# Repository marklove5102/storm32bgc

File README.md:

STorM32 BGC
===========

<strong>STM32 32-bit microcontroller based 3-axis brushless gimbal controller board</strong>

schemes and designs by OlliW (except of STorM32 v4.1)<br>
v0.17: layout by Martinez and OlliW<br>
v4.1: design by KrattWorks

latest board version: v3.3, v4.1, v6.2

The STorM32 BGC boards and all other hardware published here are open source hardware, under the terms of the TAPR Open Hardware License as published by the Free Hardware Foundation, see http://www.tapr.org/ohl.html.

The firmwares are free and the GUI is open source, for the details of the terms of usage/licenses see <a href="http://www.olliw.eu/2013/storm32bgc">here</a>.

<strong>Further resources:</strong><br>- project web page http://www.olliw.eu/2013/storm32bgc (out-dated)/<br>- thread at rcgroups http://www.rcgroups.com/forums/showthread.php?t=2055844<br>- wiki for the documentation http://www.olliw.eu/storm32bgc-wiki/

## STorM32 v6.2 Board

General purpose boards specifically made for NT and TSTorM32 setups. STM32H7 based.

## STorM32 v4.1 Board

General purpose board, like v3.3 but with on-board motor drivers.

## STorM32 v3.3 Boards

General purpose boards specifically made for NT and TSTorM32 setups.

### STorM32 Micro Series

Series of stackable boards with 20x20 mm hole pattern: Main board, NT Motor-Encoder module, NT Triple Motor module, NT Logger module. 

<strong>changes in v3.3:</strong><br>- board specifically designed for NT and T-STorM32<br>- no motor drivers on board<br>- 3 NT plugs to make it easy to connect several NT modules<br>- NT-X plug carrying also the battery voltage<br>- 5 V power rail on the NT bus, with sufficient "juice"<br>- Rx&Tx on NT bus swapped, to avoid cable crossing to connect with NT modules<br>- support of stacking with a "high-power" extension board<br>- MPU9250 on board, spi (no i2c anymore!)<br>- firmware update procedure via USB<br>- ESP8266 port for WIFI connectability<br>- CAN bus port<br>- no BOOT0 button, smaller RESET button<br>- 0402 size parts<br>- board size as small as I could get it with a 2 layer design: 40 x 25 mm<br>- mounting holes, 3 mm diameter, 35 mm apart

## v1.x Boards

These boards will be phased out.

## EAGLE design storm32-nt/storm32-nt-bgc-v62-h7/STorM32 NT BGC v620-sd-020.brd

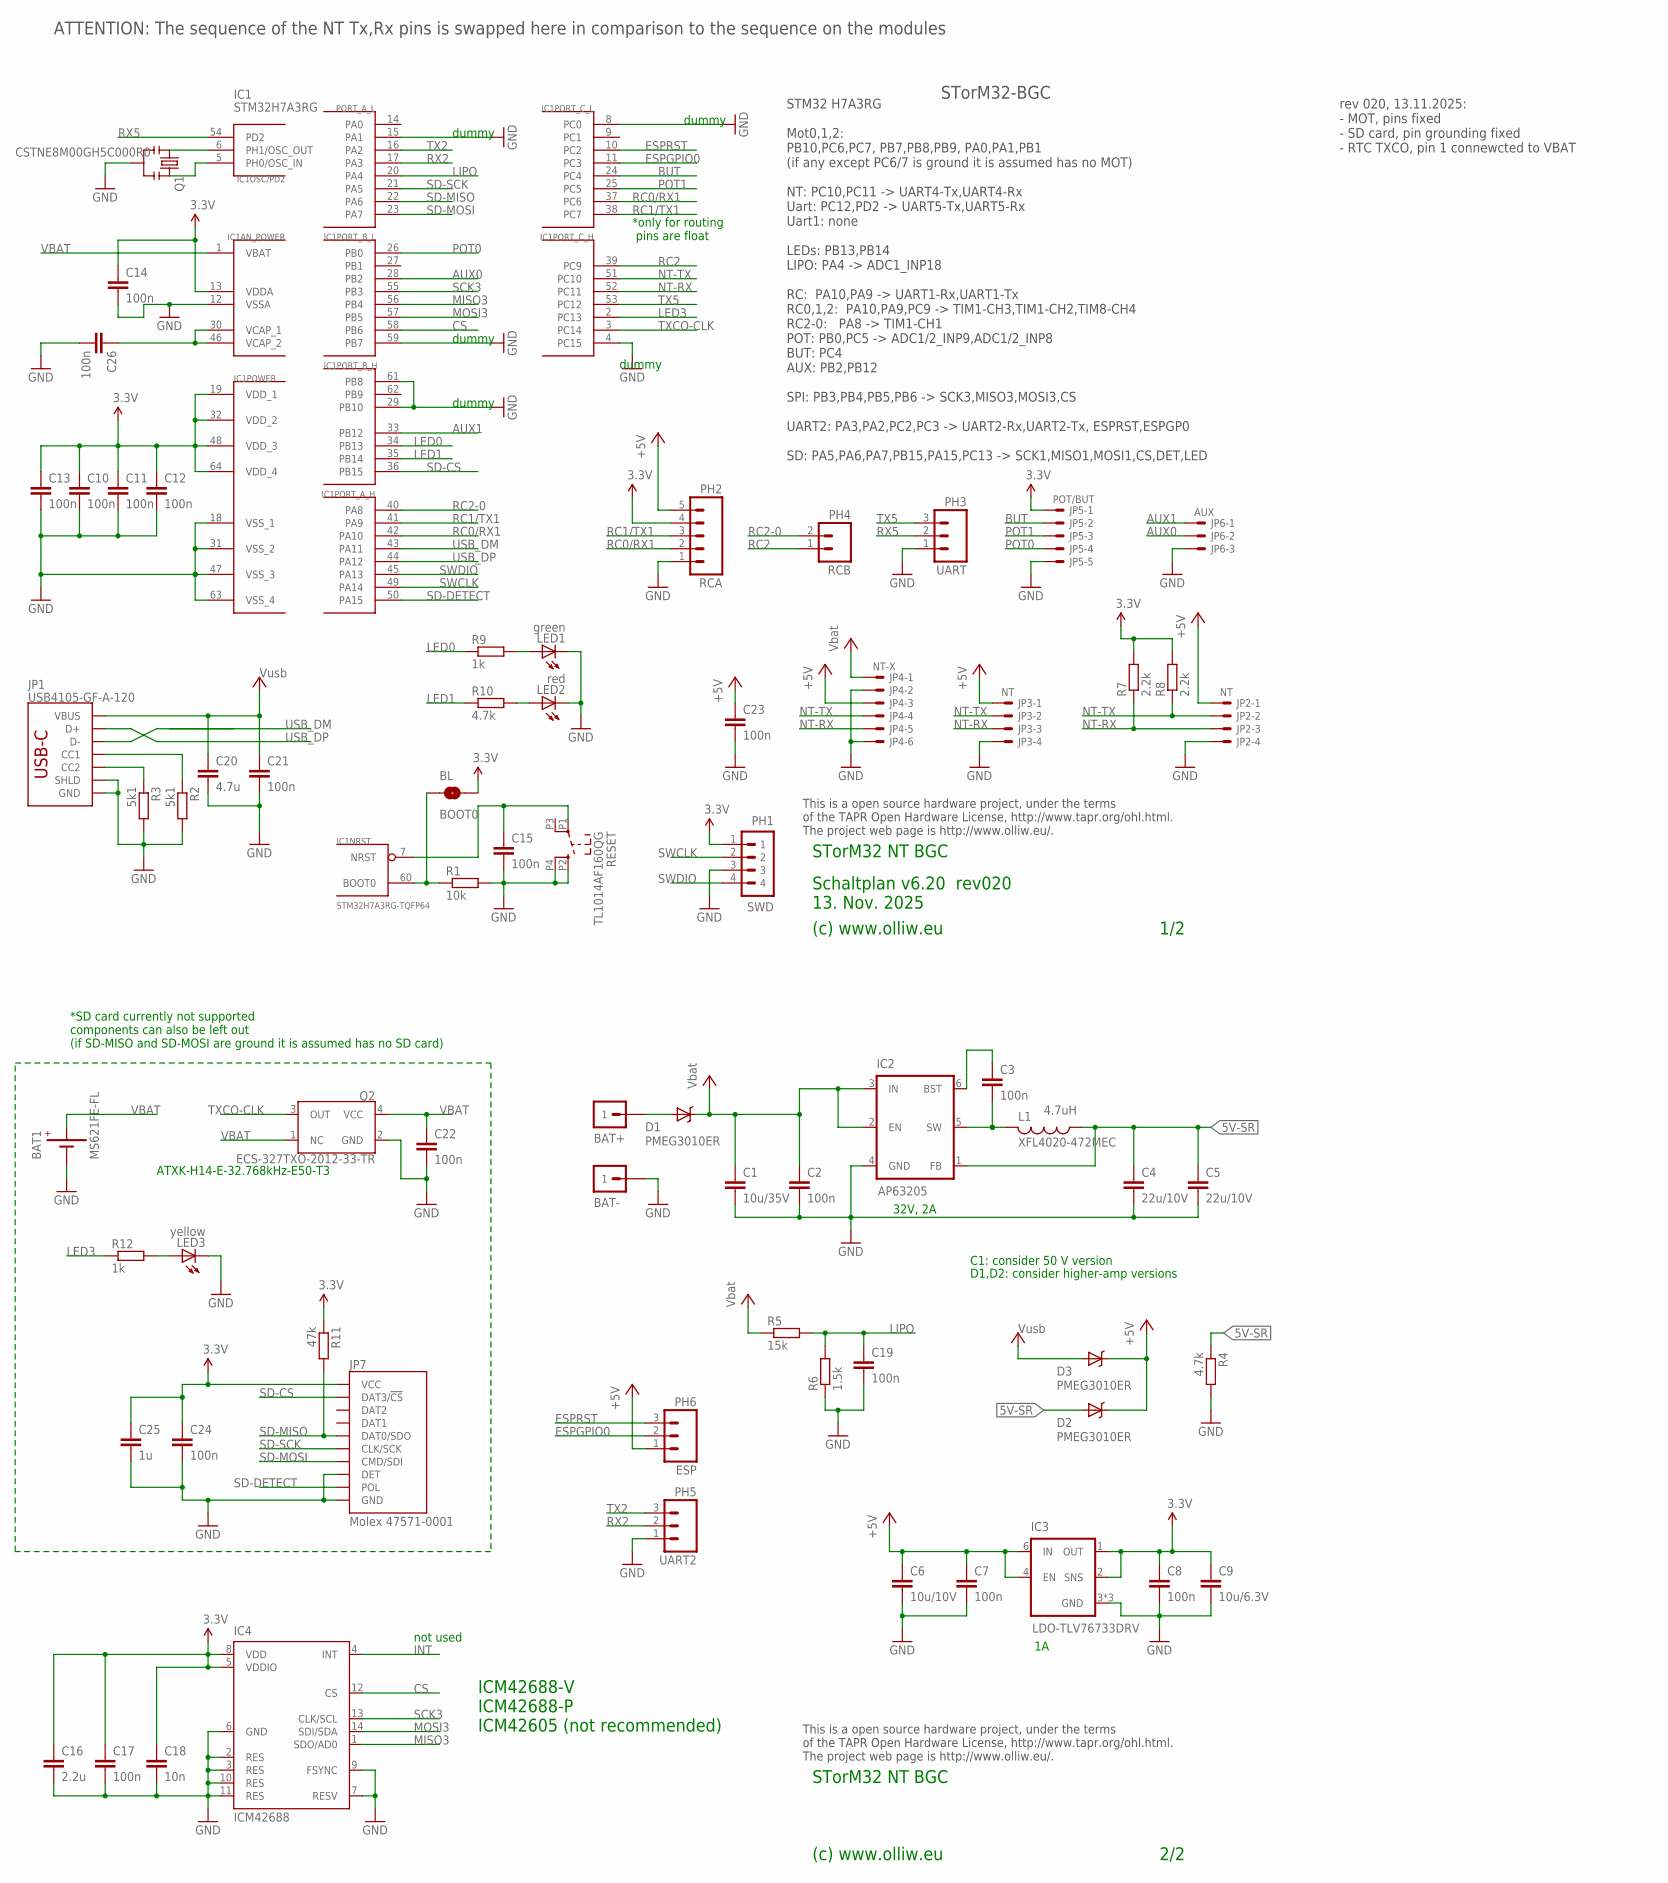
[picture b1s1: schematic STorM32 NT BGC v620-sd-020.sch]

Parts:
BAT1: MS621FE-FL; CELL-RECHARGABLE-6P8
BAT+: M1X1; 1X1_WITHOUT
BAT-: M1X1; 1X1_WITHOUT
BL: BOOT0; SJ_2S-NO
C1: 10u/35V; C1206K
C2: 100n; C0603
C3, C7, C8, C10, C11, C12, C13, C14, C15, C17, C19, C21, C22, C23, C24, C26: 100n; C0402
C4, C5: 22u/10V; C0805K
C6: 10u/10V; C0805K
C9: 10u/6.3V; C0805K
C16: 2.2u; C0603
C18: 10n; C0402
C20: 4.7u; C0603
C25: 1u; C0402
D1, D2, D3: PMEG3010ER; SOD123W-DIODE
IC1: STM32H7A3RG-TQFP64; TQFP64
IC2: AP63205; SOT23-6
IC3: LDO-TLV76733DRV; WSON-6-2X2
IC4: ICM42688; LGA14-2.5X3
JP1: USB4105-GF-A-120; USB-C
JP2, JP3: NT; SM04B-SRSS-TB
JP4: NT-X; SM06B-SRSS-TB
JP5: POT/BUT; SM05B-SRSS-TB
JP6: AUX; SM03B-SRSS-TB
JP7: Molex 47571-0001; SD-MICRO-SHORT
L1: XFL4020-472MEC; L4X4
LED1: green; CHIPLED_0603
LED2: red; CHIPLED_0603
LED3: yellow; CHIPLED_0603
PH1: SWD; 4X1_1P27_OCT_BILEX
PH2: RCA; 1X05
PH3: UART; 1X03_NO_SILK
PH4: RCB; 1X02_NO_SILK
PH5: UART2; 1X03_NO_SILK
PH6: ESP; 1X03_NO_SILK
Q1: CSTNE8M00GH5C000R0; RESONATOR-SMD
Q2: ECS-327TXO-2012-33-TR; TXCO-20X12
R1: 10k; R0402
R2, R3: 5k1; R0402
R4, R10: 4.7k; R0402
R5: 15k; R0402
R6: 1.5k; R0402
R7, R8: 2.2k; R0402
R9, R12: 1k; R0402
R11: 47k; R0402
RESET: TL1014AF160QG; TACTILE-SWITCH-SMD-RIGHT-TL1014

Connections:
3.3V: BL.2, C8.1, C9.1, C10.1, C11.1, C12.1, C13.1, C14.1, C16.1, C17.1, C18.1, C24.1, C25.1, IC1.13 (VDDA), IC1.19 (VDD_1), IC1.32 (VDD_2), IC1.48 (VDD_3), IC1.64 (VDD_4), IC3.1 (OUT), IC3.2 (SNS), IC4.5 (VDDIO), IC4.8 (VDD), JP5.1, JP7.4 (VCC), PH1.1, PH2.4, R7.2, R8.2, R11.1
5V-SR: C4.1, C5.1, D2.A, IC2.1 (FB), L1.1, R4.1
+5V: C6.1, C7.1, C23.1, D2.C, D3.C, IC3.4 (EN), IC3.6 (IN), JP2.1, JP3.1, JP4.3, PH2.5, PH6.1
AUX0: IC1.28 (PB2), JP6.2
AUX1: IC1.33 (PB12), JP6.1
BATP: BAT+.1, D1.A
BOOT0: BL.1, IC1.60 (BOOT0), R1.1
BUT: IC1.24 (PC4), JP5.2
CS: IC1.58 (PB6), IC4.12 (CS)
ESPGPIO0: IC1.11 (PC3), PH6.2
ESPRST: IC1.10 (PC2), PH6.3
GND: BAT1.P- (GND), BAT-.1, C1.2, C2.2, C4.2, C5.2, C6.2, C7.2, C8.2, C9.2, C10.2, C11.2, C12.2, C13.2, C14.2, C15.2, C16.2, C17.2, C18.2, C19.2, C20.2, C21.2, C22.2, C23.2, C24.2, C25.2, C26.2, IC1.4 (PC15), IC1.8 (PC0), IC1.12 (VSSA), IC1.15 (PA1), IC1.18 (VSS_1), IC1.29 (PB10), IC1.31 (VSS_2), IC1.47 (VSS_3), IC1.59 (PB7), IC1.61 (PB8), IC1.63 (VSS_4), IC2.4 (GND), IC3.3 (GND), IC3.5 (GND), IC3.7 (GND), IC4.2 (RES), IC4.3 (RES), IC4.6 (GND), IC4.7 (RESV), IC4.9 (FSYNC), IC4.10 (RES), IC4.11 (RES), JP1.GND, JP1.GND2 (GND), JP1.SHLD1 (SHLD), JP1.SHLD2 (SHLD), JP1.SHLD3 (SHLD), JP1.SHLD4 (SHLD), JP2.4, JP3.4, JP4.2, JP4.6, JP5.5, JP6.3, JP7.6 (GND), JP7.G4 (DET), JP7.GND1 (GND), JP7.GND2 (GND), LED1.C, LED2.C, LED3.C, PH1.3, PH2.1, PH3.1, PH5.1, Q1.2, Q2.2 (GND), R1.2, R2.2, R3.2, R4.2, R6.1, RESET.P2 (1), RESET.P4 (2)
INT: IC4.4 (INT)
LED0: IC1.34 (PB13), R9.1
LED1: IC1.35 (PB14), R10.1
LED3: IC1.2 (PC13), R12.1
LIPO: C19.1, IC1.20 (PA4), R5.2, R6.2
MISO3: IC1.56 (PB4), IC4.1 (SDO/AD0)
MOSI3: IC1.57 (PB5), IC4.14 (SDI/SDA)
unnamed: IC1.5 (PH0/OSC_IN), Q1.3
unnamed: LED3.A, R12.2
unnamed: LED1.A, R9.2
unnamed: LED2.A, R10.2
unnamed: JP1.A5 (CC1), R2.1
unnamed: JP1.B5 (CC2), R3.1
unnamed: IC1.6 (PH1/OSC_OUT), Q1.1
unnamed: C3.1, IC2.6 (BST)
unnamed: C3.2, IC2.5 (SW), L1.2
NRST: C15.1, IC1.7 (NRST), RESET.P1 (3)
NT-RX: IC1.52 (PC11), JP2.3, JP3.3, JP4.5, R7.1
NT-TX: IC1.51 (PC10), JP2.2, JP3.2, JP4.4, R8.1
POT0: IC1.26 (PB0), JP5.4
POT1: IC1.25 (PC5), JP5.3
RC0/RX1: IC1.37 (PC6), IC1.42 (PA10), PH2.2
RC1/TX1: IC1.38 (PC7), IC1.41 (PA9), PH2.3
RC2: IC1.39 (PC9), PH4.1
RC2-0: IC1.40 (PA8), PH4.2
RX2: IC1.17 (PA3), PH5.2
RX5: IC1.54 (PD2), PH3.2
SCK3: IC1.55 (PB3), IC4.13 (CLK/SCL)
SD-CS: IC1.36 (PB15), JP7.2 (DAT3/!CS!)
SD-DETECT: IC1.50 (PA15), JP7.G3 (POL)
SD-MISO: IC1.22 (PA6), JP7.7 (DAT0/SDO), R11.2
SD-MOSI: IC1.23 (PA7), JP7.3 (CMD/SDI)
SD-SCK: IC1.21 (PA5), JP7.5 (CLK/SCK)
SWCLK: IC1.49 (PA14), PH1.2
SWDIO: IC1.45 (PA13), PH1.4
TX2: IC1.16 (PA2), PH5.3
TX5: IC1.53 (PC12), PH3.3
TXCO-CLK: IC1.3 (PC14), Q2.3 (OUT)
USB_DM: IC1.43 (PA11), JP1.A7 (D-), JP1.B7 (D-)
USB_DP: IC1.44 (PA12), JP1.A6 (D+), JP1.B6 (D+)
VBAT: BAT1.P+ (BAT+), C22.1, IC1.1 (VBAT), Q2.1 (NC), Q2.4 (VCC)
VCAP_1: C26.1, IC1.30 (VCAP_1), IC1.46 (VCAP_2)
VCC: C1.1, C2.1, D1.C, IC2.2 (EN), IC2.3 (IN), JP4.1, R5.1
VUSB: C20.1, C21.1, D3.A, JP1.VBUS1 (VBUS), JP1.VBUS2 (VBUS)

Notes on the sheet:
(c) www.olliw.eu
STorM32 NT BGC
This is a open source hardware project, under the terms of the TAPR Open Hardware License, http://www.tapr.org/ohl.html. The project web page is http://www.olliw.eu/.
STM32 H7A3RG Mot0,1,2: PB10,PC6,PC7, PB7,PB8,PB9, PA0,PA1,PB1 (if any except PC6/7 is ground it is assumed has no MOT) NT: PC10,PC11 -> UART4-Tx,UART4-Rx Uart: PC12,PD2 -> UART5-Tx,UART5-Rx Uart1: none LEDs: PB13,PB14 LIPO: PA4 -> ADC1_INP18 RC: PA10,PA9 -> UART1-Rx,UART1-Tx RC0,1,2: PA10,PA9,PC9 -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
STM32H7A3RG
STorM32-BGC
1/2
2/2
IC1
ATTENTION: The sequence of the NT Tx,Rx pins is swapped here in comparison to the sequence on the modules
Schaltplan v6.20 rev020 13. Nov. 2025
4.7uH
dummy
ICM42688-V ICM42688-P ICM42605 (not recommended)
not used
*SD card currently not supported components can also be left out (if SD-MISO and SD-MOSI are ground it is assumed has no SD card)
ATXK-H14-E-32.768kHz-E50-T3
C1: consider 50 V version
32V, 2A
D1,D2: consider higher-amp versions
*only for routing pins are float
rev 020, 13.11.2025: - MOT, pins fixed - SD card, pin grounding fixed - RTC TXCO, pin 1 connewcted to VBAT

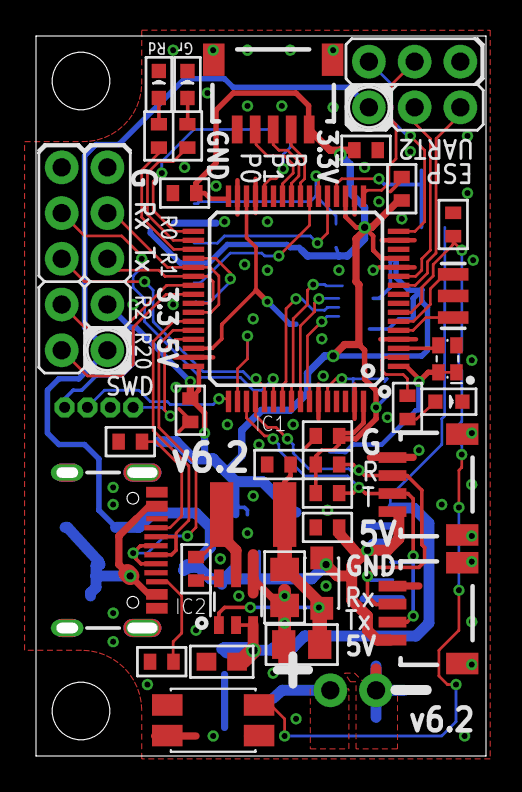
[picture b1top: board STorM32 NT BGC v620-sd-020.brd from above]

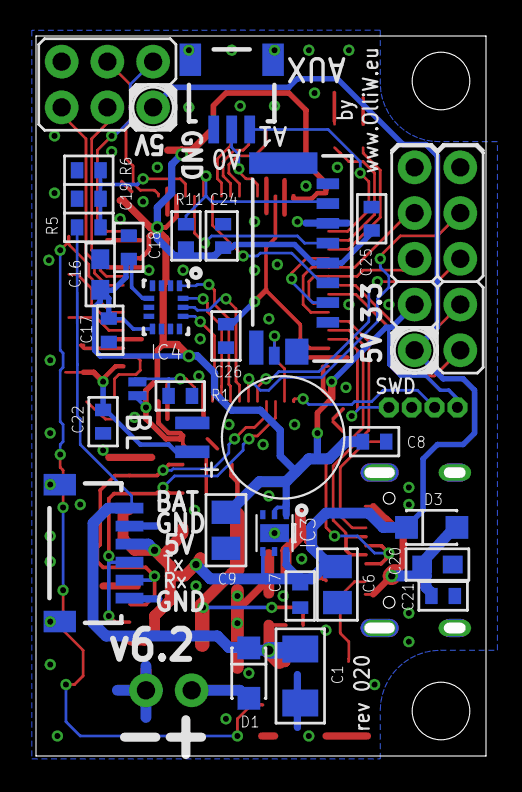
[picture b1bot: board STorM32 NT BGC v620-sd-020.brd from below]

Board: 2 copper layers, 25.0 x 40.0 mm, 69 parts (28 on the bottom side), 55 nets.

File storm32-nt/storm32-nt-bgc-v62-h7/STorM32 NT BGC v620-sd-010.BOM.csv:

"Part";"Value";"Device";"Package";"Description";"";
"BAT+";"";"M1X1";"1X1_WITHOUT";"";"";
"BAT-";"";"M1X1";"1X1_WITHOUT";"";"";
"BAT1";"MS621FE-FL";"CELL-SMD-6P8";"CELL-RECHARGABLE-6P8";"";"";
"BL";"BOOT0";"SOLDERJUMPERNO";"SJ_2S-NO";"Solder Jumper";"";
"C1";"10u/35V";"C-EUC1206K";"C1206K";"CAPACITOR, European symbol";"";
"C2";"100n";"C-EUC0603";"C0603";"CAPACITOR, European symbol";"";
"C3";"100n";"C-EUC0402";"C0402";"CAPACITOR, European symbol";"";
"C4";"22u/10V";"C-EUC0805K";"C0805K";"CAPACITOR, European symbol";"";
"C5";"22u/10V";"C-EUC0805K";"C0805K";"CAPACITOR, European symbol";"";
"C6";"10u/10V";"C-EUC0805K";"C0805K";"CAPACITOR, European symbol";"";
"C7";"100n";"C-EUC0402";"C0402";"CAPACITOR, European symbol";"";
"C8";"100n";"C-EUC0402";"C0402";"CAPACITOR, European symbol";"";
"C9";"10u/6.3V";"C-EUC0805K";"C0805K";"CAPACITOR, European symbol";"";
"C10";"100n";"C-EUC0402";"C0402";"CAPACITOR, European symbol";"";
"C11";"100n";"C-EUC0402";"C0402";"CAPACITOR, European symbol";"";
"C12";"100n";"C-EUC0402";"C0402";"CAPACITOR, European symbol";"";
"C13";"100n";"C-EUC0402";"C0402";"CAPACITOR, European symbol";"";
"C14";"100n";"C-EUC0402";"C0402";"CAPACITOR, European symbol";"";
"C15";"100n";"C-EUC0402";"C0402";"CAPACITOR, European symbol";"";
"C16";"2.2u";"C-EUC0603";"C0603";"CAPACITOR, European symbol";"";
"C17";"100n";"C-EUC0402";"C0402";"CAPACITOR, European symbol";"";
"C18";"10n";"C-EUC0402";"C0402";"CAPACITOR, European symbol";"";
"C19";"100n";"C-EUC0402";"C0402";"CAPACITOR, European symbol";"";
"C20";"4.7u";"C-EUC0603";"C0603";"CAPACITOR, European symbol";"";
"C21";"100n";"C-EUC0402";"C0402";"CAPACITOR, European symbol";"";
"C22";"100n";"C-EUC0402";"C0402";"CAPACITOR, European symbol";"";
"C23";"100n";"C-EUC0402";"C0402";"CAPACITOR, European symbol";"";
"C24";"100n";"C-EUC0402";"C0402";"CAPACITOR, European symbol";"";
"C25";"1u";"C-EUC0402";"C0402";"CAPACITOR, European symbol";"";
"C26";"100n";"C-EUC0402";"C0402";"CAPACITOR, European symbol";"";
"D1";"PMEG3010ER";"DIODE-SCHOTTKYSOD123-W";"SOD123W-DIODE";"";"";
"D2";"PMEG3010ER";"DIODE-SCHOTTKYSOD123-W";"SOD123W-DIODE";"";"";
"D3";"PMEG3010ER";"DIODE-SCHOTTKYSOD123-W";"SOD123W-DIODE";"";"";
"IC1";"STM32H7A3RG-TQFP64";"STM32H7A3-TQFP64";"TQFP64";"";"";
"IC2";"AP63205";"AP63205";"SOT23-6";"";"";
"IC3";"LDO-TLV76733DRV";"LDO-TLV767";"WSON-6-2X2";"";"";
"IC4";"ICM42688";"ICM42605";"LGA14-2.5X3";"";"";
"JP1";"USB4105-GF-A-120";"USB-C";"USB-C";"";"";
"JP2";"NT";"SM04B-SRSS-TB";"SM04B-SRSS-TB";"Disconnectable Crimp style connector, 1.0mm pitch4 contacts";"";
"JP3";"NT";"SM04B-SRSS-TB";"SM04B-SRSS-TB";"Disconnectable Crimp style connector, 1.0mm pitch4 contacts";"";
"JP4";"NT-X";"SM06B-SRSS-TB";"SM06B-SRSS-TB";"Disconnectable Crimp style connector, 1.0mm pitch6 contacts";"";
"JP5";"POT/BUT";"SM05B-SRSS-TB";"SM05B-SRSS-TB";"Disconnectable Crimp style connector, 1.0mm pitch5 contacts";"";
"JP6";"AUX";"SM03B-SRSS-TB";"SM03B-SRSS-TB";"Disconnectable Crimp style connector, 1.0mm pitch3 contacts";"";
"JP7";"Molex 47571-0001";"SD-MICRO-DFT";"SD-MICRO-SHORT";"";"";
"L1";"XFL4020-472MEC";"L";"L4X4";"";"";
"LED1";"green";"LEDCHIPLED_0603";"CHIPLED_0603";"LED";"";
"LED2";"red";"LEDCHIPLED_0603";"CHIPLED_0603";"LED";"";
"LED3";"yellow";"LEDCHIPLED_0603";"CHIPLED_0603";"LED";"";
"PH1";"SWD";"P4X1_1P27-OCT_BILEX";"4X1_1P27_OCT_BILEX";"";"";
"PH2";"RCA";"M05PTH";"1X05";"Header 5";"";
"PH3";"UART";"M031X03_NO_SILK";"1X03_NO_SILK";"Header 3";"";
"PH4";"RCB";"M021X02_NO_SILK";"1X02_NO_SILK";"Header 2";"";
"PH5";"UART2";"M031X03_NO_SILK";"1X03_NO_SILK";"Header 3";"";
"PH6";"ESP";"M031X03_NO_SILK";"1X03_NO_SILK";"Header 3";"";
"Q1";"CSTNE8M00GH5C000R0";"RESONATORSMD";"RESONATOR-SMD";"Resonator";"";
"Q2";"ECS-327TXO-2012-33-TR";"TXCO-2.0X1.2MM";"TXCO-20X12";"";"";
"R1";"10k";"R-EU_R0402";"R0402";"RESISTOR, European symbol";"";
"R2";"5k1";"R-EU_R0402";"R0402";"RESISTOR, European symbol";"";
"R3";"5k1";"R-EU_R0402";"R0402";"RESISTOR, European symbol";"";
"R4";"4.7k";"R-EU_R0402";"R0402";"RESISTOR, European symbol";"";
"R5";"15k";"R-EU_R0402";"R0402";"RESISTOR, European symbol";"";
"R6";"1.5k";"R-EU_R0402";"R0402";"RESISTOR, European symbol";"";
"R7";"2.2k";"R-EU_R0402";"R0402";"RESISTOR, European symbol";"";
"R8";"2.2k";"R-EU_R0402";"R0402";"RESISTOR, European symbol";"";
"R9";"1k";"R-EU_R0402";"R0402";"RESISTOR, European symbol";"";
"R10";"4.7k";"R-EU_R0402";"R0402";"RESISTOR, European symbol";"";
"R11";"47k";"R-EU_R0402";"R0402";"RESISTOR, European symbol";"";
"R12";"1k";"R-EU_R0402";"R0402";"RESISTOR, European symbol";"";
"RESET";"TL1014AF160QG";"SWITCH-SMD-RIGHT-TL1014";"TACTILE-SWITCH-SMD-RIGHT-TL1014";"";"";

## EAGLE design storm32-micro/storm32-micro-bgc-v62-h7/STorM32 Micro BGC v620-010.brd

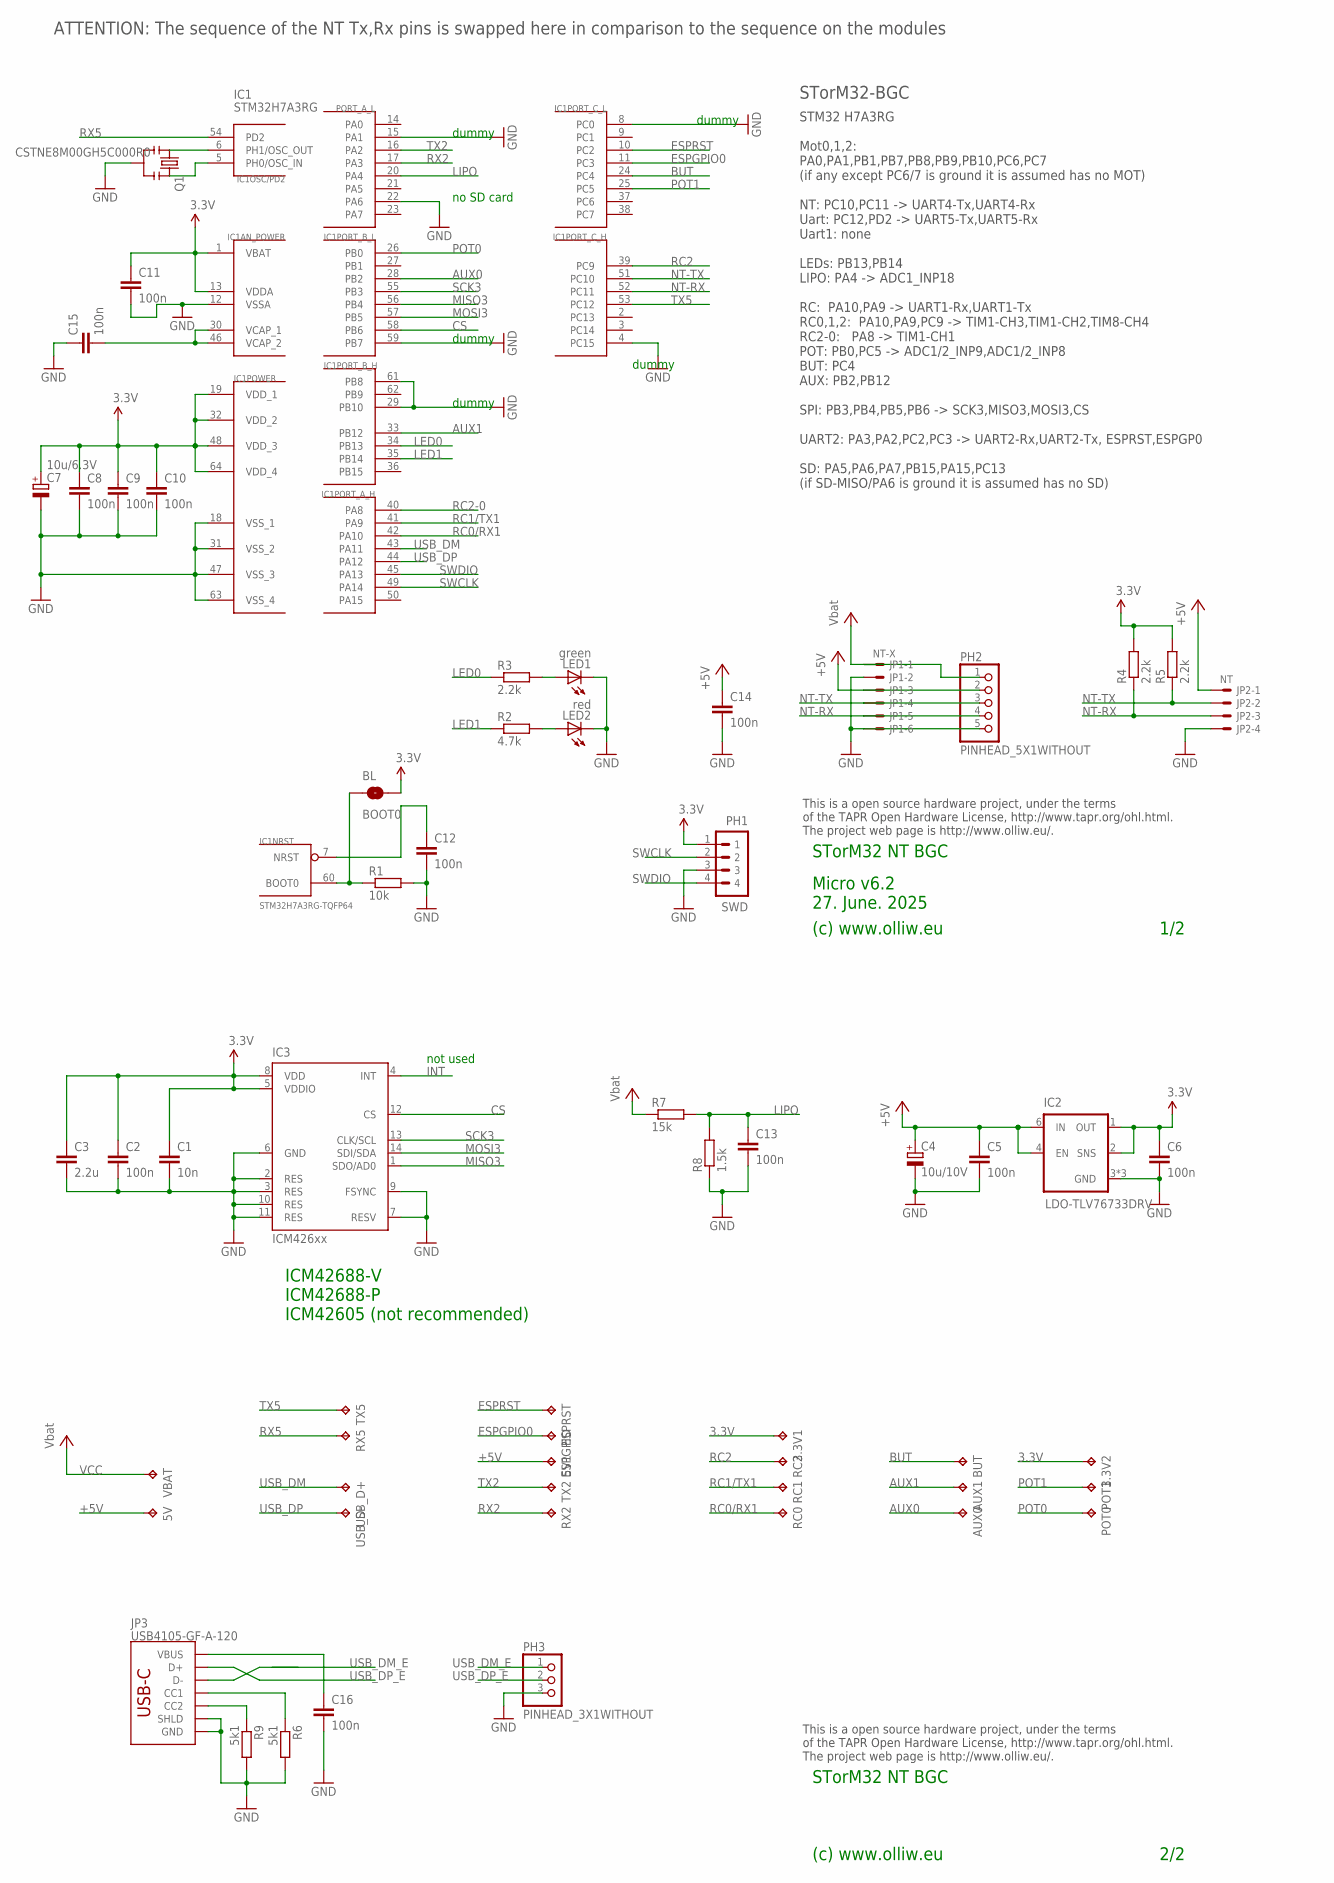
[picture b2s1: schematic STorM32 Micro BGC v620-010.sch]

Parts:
3.3V1, 3.3V2, 5V, 5V1: TPB1,27; B1,27
AUX0, AUX1: TPB1,27; B1,27
BL: BOOT0; SJ_2S-NO
BUT: TPB1,27; B1,27
C1: 10n; C0402
C2, C6, C8, C9, C10, C11, C12, C13, C14, C15, C16: 100n; C0402
C3: 2.2u; C0603
C4: 10u/10V; SMC_A
C5: 100n; C0603
C7: 10u/6.3V; SMC_A
ESPGPIO: TPB1,27; B1,27
ESPRST: TPB1,27; B1,27
IC1: STM32H7A3RG-TQFP64; TQFP64
IC2: LDO-TLV76733DRV; WSON-6-2X2
IC3: ICM426xx; LGA14-2.5X3
JP1: NT-X; SM06B-SRSS-TB
JP2: NT; SM04B-SRSS-TB
JP3: USB4105-GF-A-120; USB-C
LED1: green; CHIPLED_0603
LED2: red; CHIPLED_0603
PH1: SWD; 4X1_1P27_OCT_BILEX
PH2: PINHEAD_5X1WITHOUT; PINHEAD_5X1_WO
PH3: PINHEAD_3X1WITHOUT; PINHEAD_3X1_WO
POT0, POT1: TPB1,27; B1,27
Q1: CSTNE8M00GH5C000R0; RESONATOR-SMD
R1: 10k; R0402
R2: 4.7k; R0402
R3, R4, R5: 2.2k; R0402
R6, R9: 5k1; R0402
R7: 15k; R0402
R8: 1.5k; R0402
RC0, RC1, RC2: TPB1,27; B1,27
RX2, RX5: TPB1,27; B1,27
TX2, TX5: TPB1,27; B1,27
USB_D+: TPB1,27; B1,27
USB_D-: TPB1,27; B1,27
VBAT: TPB1,27; B1,27

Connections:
3.3V: 3.3V1.TP, 3.3V2.TP, BL.2, C1.1, C2.1, C3.1, C6.1, C7.+, C8.1, C9.1, C10.1, C11.1, IC1.1 (VBAT), IC1.13 (VDDA), IC1.19 (VDD_1), IC1.32 (VDD_2), IC1.48 (VDD_3), IC1.64 (VDD_4), IC2.1 (OUT), IC2.2 (SNS), IC3.5 (VDDIO), IC3.8 (VDD), PH1.1, R4.2, R5.2
+5V: 5V.TP, 5V1.TP, C4.+, C5.1, C14.1, IC2.4 (EN), IC2.6 (IN), JP1.3, JP2.1, PH2.2
AUX0: AUX0.TP, IC1.28 (PB2)
AUX1: AUX1.TP, IC1.33 (PB12)
BOOT0: BL.1, IC1.60 (BOOT0), R1.1
BUT: BUT.TP, IC1.24 (PC4)
CS: IC1.58 (PB6), IC3.12 (CS)
ESPGPIO0: ESPGPIO.TP, IC1.11 (PC3)
ESPRST: ESPRST.TP, IC1.10 (PC2)
GND: C1.2, C2.2, C3.2, C4.-, C5.2, C6.2, C7.-, C8.2, C9.2, C10.2, C11.2, C12.2, C13.2, C14.2, C15.1, C16.2, IC1.4 (PC15), IC1.8 (PC0), IC1.12 (VSSA), IC1.15 (PA1), IC1.18 (VSS_1), IC1.22 (PA6), IC1.29 (PB10), IC1.31 (VSS_2), IC1.47 (VSS_3), IC1.59 (PB7), IC1.61 (PB8), IC1.63 (VSS_4), IC2.3 (GND), IC2.5 (GND), IC2.7 (GND), IC3.2 (RES), IC3.3 (RES), IC3.6 (GND), IC3.7 (RESV), IC3.9 (FSYNC), IC3.10 (RES), IC3.11 (RES), JP1.2, JP1.6, JP2.4, JP3.GND, JP3.GND2 (GND), JP3.SHLD1 (SHLD), JP3.SHLD2 (SHLD), JP3.SHLD3 (SHLD), JP3.SHLD4 (SHLD), LED1.C, LED2.C, PH1.3, PH2.5, PH3.3 (5), Q1.2, R1.2, R6.2, R8.1, R9.2
INT: IC3.4 (INT)
LED0: IC1.34 (PB13), R3.1
LED1: IC1.35 (PB14), R2.1
LIPO: C13.1, IC1.20 (PA4), R7.2, R8.2
MISO3: IC1.56 (PB4), IC3.1 (SDO/AD0)
MOSI3: IC1.57 (PB5), IC3.14 (SDI/SDA)
unnamed: JP3.B5 (CC2), R9.1
unnamed: C16.1, JP3.VBUS1 (VBUS), JP3.VBUS2 (VBUS)
unnamed: LED1.A, R3.2
unnamed: LED2.A, R2.2
unnamed: JP3.A5 (CC1), R6.1
unnamed: IC1.5 (PH0/OSC_IN), Q1.3
unnamed: IC1.6 (PH1/OSC_OUT), Q1.1
NRST: C12.1, IC1.7 (NRST)
NT-RX: IC1.52 (PC11), JP1.5, JP2.3, PH2.4, R4.1
NT-TX: IC1.51 (PC10), JP1.4, JP2.2, PH2.3, R5.1
POT0: IC1.26 (PB0), POT0.TP
POT1: IC1.25 (PC5), POT1.TP
RC0/RX1: IC1.42 (PA10), RC0.TP
RC1/TX1: IC1.41 (PA9), RC1.TP
RC2: IC1.39 (PC9), RC2.TP
RC2-0: IC1.40 (PA8)
RX2: IC1.17 (PA3), RX2.TP
RX5: IC1.54 (PD2), RX5.TP
SCK3: IC1.55 (PB3), IC3.13 (CLK/SCL)
SWCLK: IC1.49 (PA14), PH1.2
SWDIO: IC1.45 (PA13), PH1.4
TX2: IC1.16 (PA2), TX2.TP
TX5: IC1.53 (PC12), TX5.TP
USB_DM: IC1.43 (PA11), USB_D+.TP
USB_DM_E: JP3.A7 (D-), JP3.B7 (D-), PH3.1
USB_DP: IC1.44 (PA12), USB_D-.TP
USB_DP_E: JP3.A6 (D+), JP3.B6 (D+), PH3.2 (3)
VCAP_1: C15.2, IC1.30 (VCAP_1), IC1.46 (VCAP_2)
VCC: JP1.1, PH2.1, R7.1, VBAT.TP

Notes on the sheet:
(c) www.olliw.eu
STorM32 NT BGC
This is a open source hardware project, under the terms of the TAPR Open Hardware License, http://www.tapr.org/ohl.html. The project web page is http://www.olliw.eu/.
STM32H7A3RG
STorM32-BGC
1/2
2/2
IC1
ATTENTION: The sequence of the NT Tx,Rx pins is swapped here in comparison to the sequence on the modules
dummy
Micro v6.2 27. June. 2025
STM32 H7A3RG Mot0,1,2: PA0,PA1,PB1,PB7,PB8,PB9,PB10,PC6,PC7 (if any except PC6/7 is ground it is assumed has no MOT) NT: PC10,PC11 -> UART4-Tx,UART4-Rx Uart: PC12,PD2 -> UART5-Tx,UART5-Rx Uart1: none LEDs: PB13,PB14 LIPO: PA4 -> ADC1_INP18 RC: PA10,PA9 -> UART1-Rx,UART1-Tx RC0,1,2: PA10,PA9,PC9 -> 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
ICM42688-V ICM42688-P ICM42605 (not recommended)
not used
no SD card

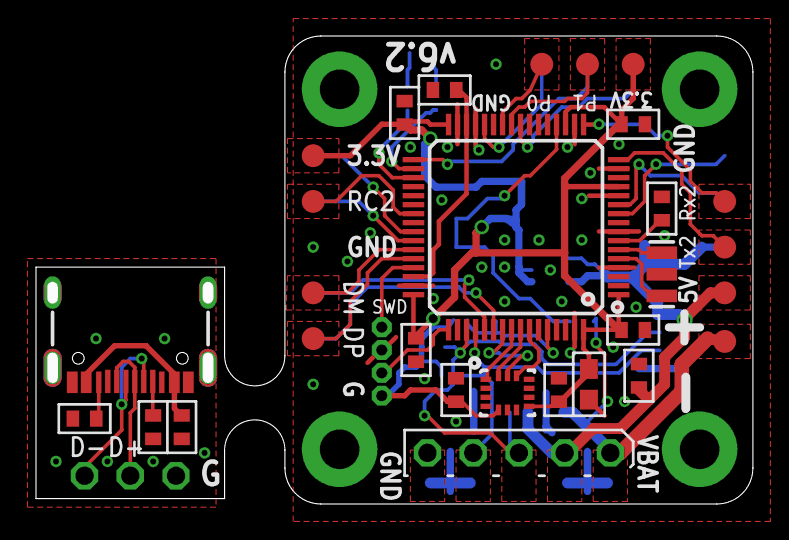
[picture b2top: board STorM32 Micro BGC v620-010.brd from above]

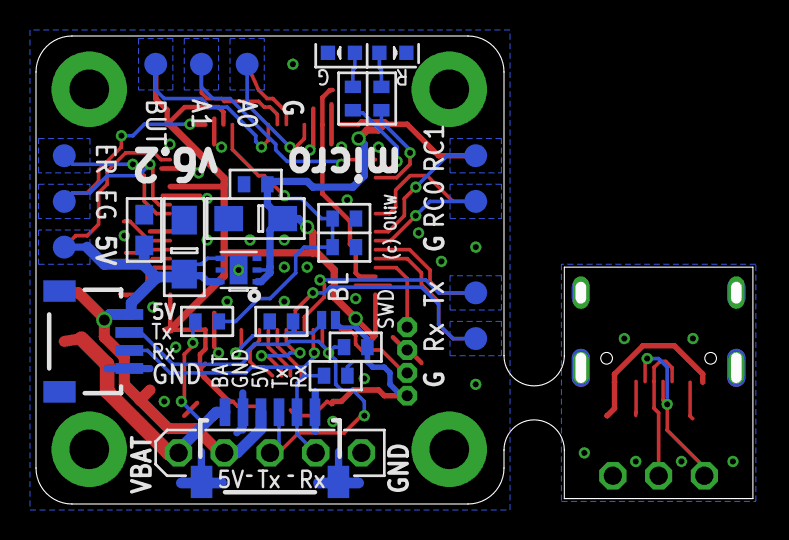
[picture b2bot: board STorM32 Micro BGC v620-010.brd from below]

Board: 2 copper layers, 39.8 x 26.0 mm, 59 parts (28 on the bottom side), 43 nets.

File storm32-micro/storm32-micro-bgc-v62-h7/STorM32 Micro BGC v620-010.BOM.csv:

"Part";"Value";"Device";"Package";"Description";"TP_SIGNAL_NAME";
"3.3V1";"TPB1,27";"TPB1,27";"B1,27";"Test pad";"";
"3.3V2";"TPB1,27";"TPB1,27";"B1,27";"Test pad";"";
"5V";"TPB1,27";"TPB1,27";"B1,27";"Test pad";"";
"5V1";"TPB1,27";"TPB1,27";"B1,27";"Test pad";"";
"AUX0";"TPB1,27";"TPB1,27";"B1,27";"Test pad";"";
"AUX1";"TPB1,27";"TPB1,27";"B1,27";"Test pad";"";
"BL";"BOOT0";"SOLDERJUMPERNO";"SJ_2S-NO";"Solder Jumper";"";
"BUT";"TPB1,27";"TPB1,27";"B1,27";"Test pad";"";
"C1";"10n";"C-EUC0402";"C0402";"CAPACITOR, European symbol";"";
"C2";"100n";"C-EUC0402";"C0402";"CAPACITOR, European symbol";"";
"C3";"2.2u";"C-EUC0603";"C0603";"CAPACITOR, European symbol";"";
"C4";"10u/10V";"CPOL-EUSMCA";"SMC_A";"POLARIZED CAPACITOR, European symbol";"";
"C5";"100n";"C-EUC0603";"C0603";"CAPACITOR, European symbol";"";
"C6";"100n";"C-EUC0402";"C0402";"CAPACITOR, European symbol";"";
"C7";"10u/6.3V";"CPOL-EUSMCA";"SMC_A";"POLARIZED CAPACITOR, European symbol";"";
"C8";"100n";"C-EUC0402";"C0402";"CAPACITOR, European symbol";"";
"C9";"100n";"C-EUC0402";"C0402";"CAPACITOR, European symbol";"";
"C10";"100n";"C-EUC0402";"C0402";"CAPACITOR, European symbol";"";
"C11";"100n";"C-EUC0402";"C0402";"CAPACITOR, European symbol";"";
"C12";"100n";"C-EUC0402";"C0402";"CAPACITOR, European symbol";"";
"C13";"100n";"C-EUC0402";"C0402";"CAPACITOR, European symbol";"";
"C14";"100n";"C-EUC0402";"C0402";"CAPACITOR, European symbol";"";
"C15";"100n";"C-EUC0402";"C0402";"CAPACITOR, European symbol";"";
"C16";"100n";"C-EUC0402";"C0402";"CAPACITOR, European symbol";"";
"ESPGPIO";"TPB1,27";"TPB1,27";"B1,27";"Test pad";"";
"ESPRST";"TPB1,27";"TPB1,27";"B1,27";"Test pad";"";
"IC1";"STM32H7A3RG-TQFP64";"STM32H7A3-TQFP64";"TQFP64";"";"";
"IC2";"LDO-TLV76733DRV";"LDO-TLV767";"WSON-6-2X2";"";"";
"IC3";"ICM426xx";"ICM42605";"LGA14-2.5X3";"";"";
"JP1";"NT-X";"SM06B-SRSS-TB";"SM06B-SRSS-TB";"Disconnectable Crimp style connector, 1.0mm pitch6 contacts";"";
"JP2";"NT";"SM04B-SRSS-TB";"SM04B-SRSS-TB";"Disconnectable Crimp style connector, 1.0mm pitch4 contacts";"";
"JP3";"USB4105-GF-A-120";"USB-C";"USB-C";"";"";
"LED1";"green";"LEDCHIPLED_0603";"CHIPLED_0603";"LED";"";
"LED2";"red";"LEDCHIPLED_0603";"CHIPLED_0603";"LED";"";
"PH1";"SWD";"P4X1_1P27-OCT_BILEX";"4X1_1P27_OCT_BILEX";"";"";
"PH2";"PINHEAD_5X1WITHOUT";"PINHEAD_5X1WITHOUT";"PINHEAD_5X1_WO";"";"";
"PH3";"PINHEAD_3X1WITHOUT";"PINHEAD_3X1WITHOUT";"PINHEAD_3X1_WO";"";"";
"POT0";"TPB1,27";"TPB1,27";"B1,27";"Test pad";"";
"POT1";"TPB1,27";"TPB1,27";"B1,27";"Test pad";"";
"Q1";"CSTNE8M00GH5C000R0";"RESONATORSMD";"RESONATOR-SMD";"Resonator";"";
"R1";"10k";"R-EU_R0402";"R0402";"RESISTOR, European symbol";"";
"R2";"4.7k";"R-EU_R0402";"R0402";"RESISTOR, European symbol";"";
"R3";"2.2k";"R-EU_R0402";"R0402";"RESISTOR, European symbol";"";
"R4";"2.2k";"R-EU_R0402";"R0402";"RESISTOR, European symbol";"";
"R5";"2.2k";"R-EU_R0402";"R0402";"RESISTOR, European symbol";"";
"R6";"5k1";"R-EU_R0402";"R0402";"RESISTOR, European symbol";"";
"R7";"15k";"R-EU_R0402";"R0402";"RESISTOR, European symbol";"";
"R8";"1.5k";"R-EU_R0402";"R0402";"RESISTOR, European symbol";"";
"R9";"5k1";"R-EU_R0402";"R0402";"RESISTOR, European symbol";"";
"RC0";"TPB1,27";"TPB1,27";"B1,27";"Test pad";"";
"RC1";"TPB1,27";"TPB1,27";"B1,27";"Test pad";"";
"RC2";"TPB1,27";"TPB1,27";"B1,27";"Test pad";"";
"RX2";"TPB1,27";"TPB1,27";"B1,27";"Test pad";"";
"RX5";"TPB1,27";"TPB1,27";"B1,27";"Test pad";"";
"TX2";"TPB1,27";"TPB1,27";"B1,27";"Test pad";"";
"TX5";"TPB1,27";"TPB1,27";"B1,27";"Test pad";"";
"USB_D+";"TPB1,27";"TPB1,27";"B1,27";"Test pad";"";
"USB_D-";"TPB1,27";"TPB1,27";"B1,27";"Test pad";"";
"VBAT";"TPB1,27";"TPB1,27";"B1,27";"Test pad";"";

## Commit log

2025-06-29 release STorM32 v6.2 board, H7 based, also Micro version released
2025-06-29 move storm32-bgc, storm32-rpihat folders to old
2025-06-29 readme
2025-07-11 release firmware v2.73e
2025-11-13 STorM32 v6.2 board, revision 020
2025-11-30 release firmware v2.74

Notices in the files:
parts and their libraries:
Licensing: CC v3.0 Share-Alike You are welcome to use this library for commercial purposes.
